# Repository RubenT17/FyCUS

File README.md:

# FyCUS

Code and schemes for FyCUS's Cubesat project.

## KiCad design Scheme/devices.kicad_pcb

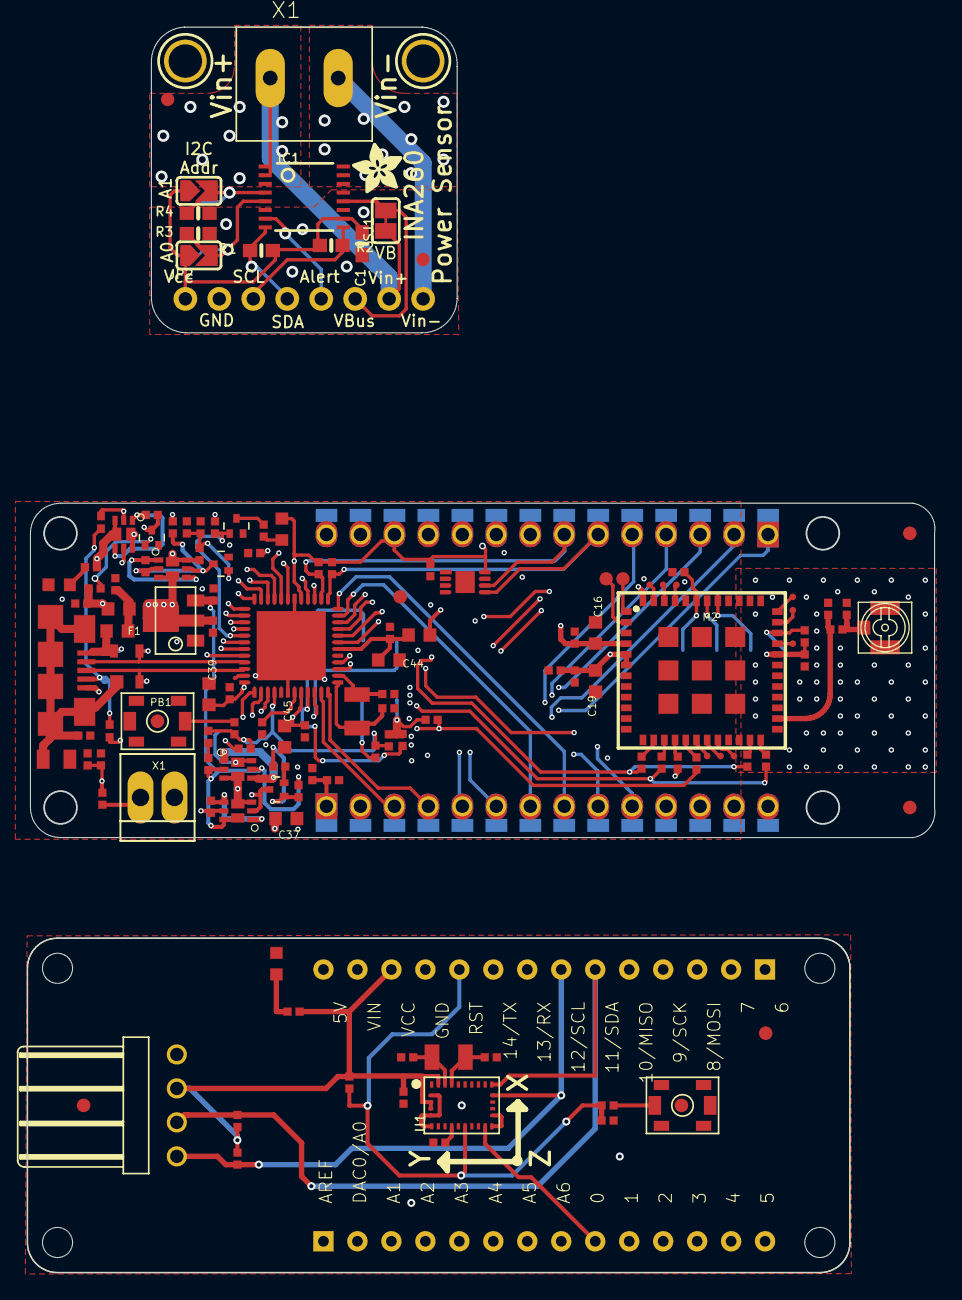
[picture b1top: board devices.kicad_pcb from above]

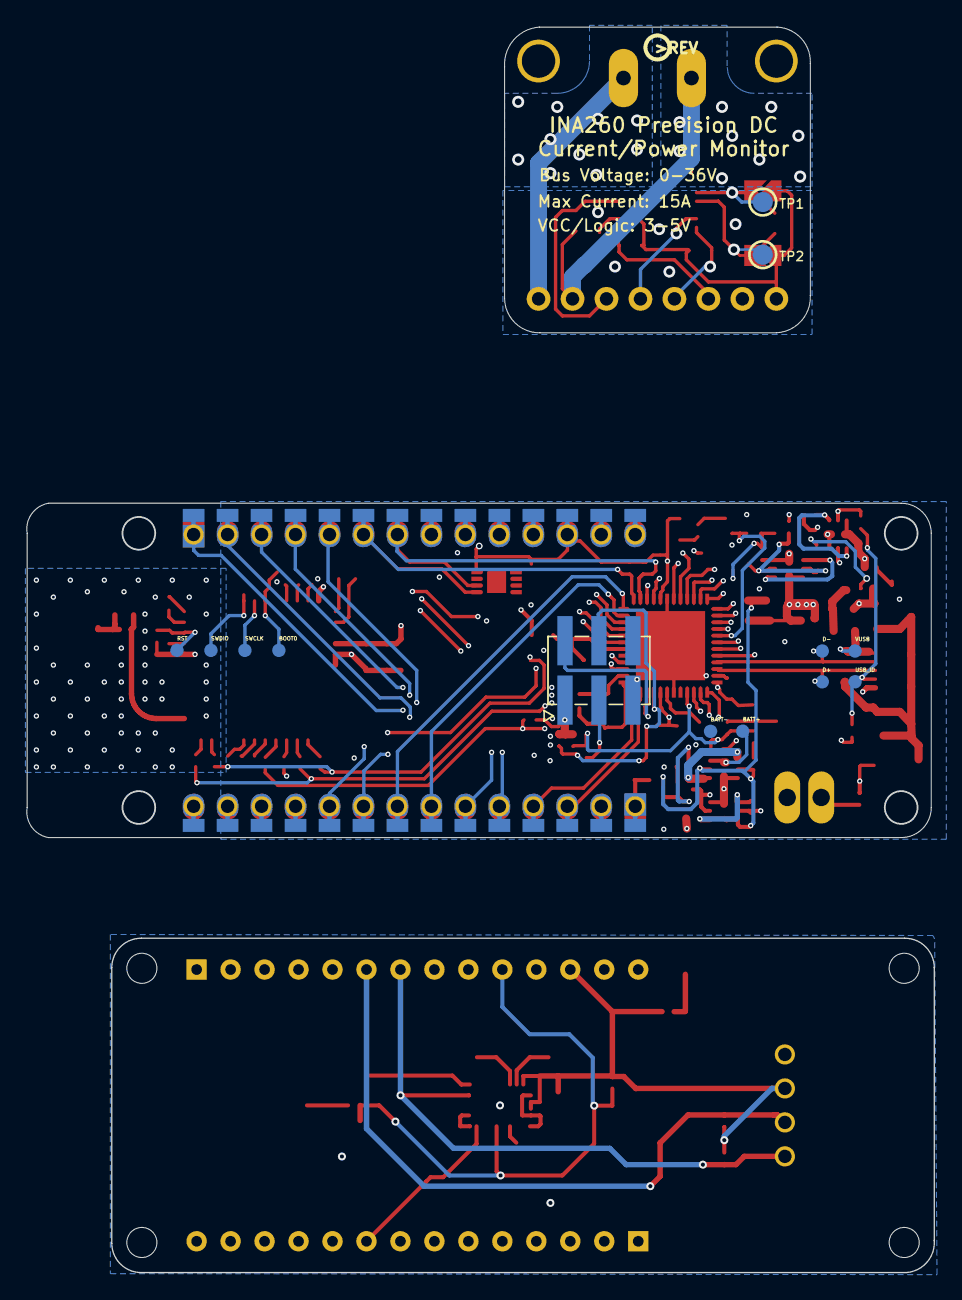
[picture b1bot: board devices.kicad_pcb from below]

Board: 2 copper layers, 67.9 x 93.1 mm, 162 parts (15 on the bottom side), 8 nets.

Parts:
@HOLE0, @HOLE1, @HOLE2, @HOLE3: (no value)
BATT+: DNP; TP-1.00MM
BATT-: DNP; TP-1.00MM
BOOT0: DNP; TP-1.00MM
C1, C3#2, C4, C5#2, C6, C8, C9, C11, C14, C18, C21, C22, C38, C40, C42, C43: 100n; 0402-1005X55N
C1#2: 4n7; 0805-R2013X50N
C1#3: 1uF; 0603-NO
C2, C3: 22p; 0402-1005X55N
C2#2: 10n; 0402-1005X55N
C4#2, C5: 20p; 0402-1005X55N
C7: 4u7; 0402-1005X55N
C10, C12: DNP; 0402-1005X55N
C15, C17, C20, C47: 1u; 0402-1005X55N
C16, C19, C37, C39, C44, C45: 10u; 0603-1608X90N
D1: PRTR5V0U2X,215; SOT190P230X110-4N
D1+, D1-: DNP; TP-1.00MM
D2, D3: PMEG2005EL; SODFL1008X40N-882D
D+: DNP; TP-1.00MM
D-: DNP; TP-1.00MM
DL1, DL2: GREEN; LEDC1608X80N-AK
DL1#2: YELLOW; LEDC1608X80N-AK
F1: PTC; 0603-1608X90N
FD1, FD1#2, FD2, FD2#2, FD3, FD3#2, FD4: DNP; FD-1-1.5
FID3, FID4: MICROBUILDER_FIDUCIAL""; MICROBUILDER_FIDUCIAL_1MM
IC1: INA260; TSSOP16
J1: USB-MICRO; ZX62-AB-5PA
J2: MODULINO-4RA; MODULINO-4-RA
J2#2: DNP; 2X3_SMT
J3, J5: DNP; 1X14_SMD_TH
J7: UFL; U.FL-R-SMT-1(60)
JP2: 1X08_ROUND_70
L1, L5: FERRITE-470R; 0603-1608X90N@1
M2: CMWX1ZZABZ-078
MKR1: DNP; MKRBOARD
PB1: RESET; C&K_PTS820_NO_HOLES
Q1, Q2, Q5, Q6: DMP2160UFDB; PWR_SC70
Q3, Q4, Q7, Q8: 2N7002T; SOTFL50P160X78-3
R1, R2#3, R3#2, R4: 10K; 0603-NO
R1#2, R2, R5: 1k; 0402-1005X55N
R1#3: 1M; 0402-1005X55N
R2#2, R3, R3#3, R4#3, R6, R7, R26, R29: 330R; 0402-1005X55N
R4#2, R5#2, R10, R11, R14, R16, R17, R27, R28: 10k; 0402-1005X55N
R8: 330k; 0402-1005X55N
R9: 680k; 0402-1005X55N
R12, R23, R24, R25, R33: 100k; 0402-1005X55N
R13: 47k; 0402-1005X55N
R18, R19: DNP; 0402-1005X55N
R20, R30, R31, R32, R34: 0R; 0402-1005X55N
R21, R22: 4k7; 0402-1005X55N
RST: DNP; TP-1.00MM
SJ1: SOLDERJUMPER_CLOSEDWIRE
SJ3, SJ4: SOLDERJUMPER_ARROW_NOPASTE
SWCLK: DNP; TP-1.00MM
SWDIO: DNP; TP-1.00MM
TP1, TP2#2: TESTPOINT_ROUND_1.5MM
TP1#2, TP2, TP3, TP4, TP5, TP6, TP7, TP15, TP18: DNP; TP-0.50MM
U1: D21G18; QFN50P700X700X90-49XN-EPSQ515
U1#2: BNO055
U2: LDO2SOT89-3L; SOT89-3L
U3: ECC508; SON50P300X200X60-9N-EP160X140
U$1: ADAFRUIT_3.5MM
U$2: PTS820; C&K_PTS820_NO_HOLES
U$5, U$6, U$7, U$8: MH_RND_F_2.2MM_NM
U$6#2: PCBFEAT-REV-040
U$7#2, U$8#2: MOUNTINGHOLE2.5; MOUNTINGHOLE_2.5_PLATED
USB_ID: DNP; TP-1.00MM
VUSB: DNP; TP-1.00MM
X1: SCREW2X2.54; SCREW2
X1#2: 5.08mm Term; TERMBLOCK_508_1X2
Y1: 32.768KHz; ABS07
Y1#2: 32768Hz; ABS07

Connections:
+3V3: C5#2.2, C11.1, C19.1, C20.1, C21.1, C22.1, C37.1, C38.1, C39.1, C40.1, C42.1, C45.1, DL1#2.A, J2.P$3, J2#2.1, J5.12, L5.1, M2.5, M2.6, M2.32, M2.48, MKR1.VCC, Q5.D2, Q5.D2', Q6.D2, Q6.D2', R1#2.2, R2.2, R3#3.2, R4#2.2, R5.2, R5#2.2, R14.2, R16.2, R21.2, R22.2, U1.17, U1.36, U1.44, U1#2.3, U1#2.4, U1#2.28, U3.8
+5V: C15.1, C16.1, C18.1, J5.14, M2.4, Q1.D2, Q1.D2', Q2.D2, Q2.D2', R29.2, U2.2, U2.TH
GND: BATT-.X, C1.1, C1#2.2, C1#3.2, C2.1, C2#2.2, C3.2, C3#2.2, C4.2, C4#2.1, C5.1, C5#2.1, C6.2, C7.2, C8.2, C9.2, C10.2, C11.2, C12.2, C14.2, C15.2, C16.2, C17.2, C18.2, C19.2, C20.2, C21.2, C22.2, C37.2, C38.2, C39.2, C40.2, C42.2, C43.2, C44.2, C45.2, C47.2, DL1.C, DL2.C, IC1.6, IC1.11, IC1.13, J1.5, J2.P$4, J2#2.5, J5.11, J7.GND1, J7.GND2, JP2.2, M2.3, M2.7, M2.25, M2.27, M2.44, M2.49, M2.50, M2.51, M2.52, M2.53, M2.54, M2.55, M2.56, M2.57, MKR1.GND, PB1.1, PB1.2, PB1.3, PB1.4, PB1.5, Q3.S, Q4.S, Q7.S, Q8.S, R1#3.1, R3#2.1, R4.1, R8.1, R10.1, R12.1, R17.1, R24.1, R33.1, U1.5, U1.18, U1.35, U1.42, U1.49, U1#2.2, U1#2.5, U1#2.6, U1#2.15, U1#2.16, U1#2.17, U1#2.18, U1#2.25, U2.1, U3.4, U3.9, U$2.1, U$2.2, U$2.3, U$2.4, U$2.5, X1.GND
USB_ID: D2.C, D3.C, J1.4, USB_ID.X
VBATT: BATT+.X, Q6.D1, Q6.D1', R9.2, X1.V+
VCC: C1#3.1, IC1.10, JP2.1, R1.1, R2#3.1, SJ3.1, SJ4.1
VIN: J5.13, Q2.D1, Q2.D1', R23.2
VUSB: C6.1, L1.2, Q1.D1, Q1.D1', R25.2

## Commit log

2022-08-17 Add files
2022-08-17 Add scheme
2022-08-22 Prueba de otro método SD
2022-08-22 Corrección GPS y delay sin bloqueo
2022-08-24 Logger for RPi
2022-08-25 Add doc documentation
2022-08-28 Pequeñas modificaciones
